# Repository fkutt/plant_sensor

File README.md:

# Czujnik wilgotności gleby (plant sensor)

Tania bateryjna sonda pojemnościowa do doniczek: ESP32-C3 SuperMini na podstawkach, ogniwo
LiFePO4 14500, elektrody wytrawione w PCB. Pomiar co godzinę, historia w sondzie, telefon przez
Bluetooth, opcjonalnie baza (drugi ESP32-C3 na USB) i Home Assistant przez MQTT.

**Aplikacja na telefon:** strona z folderu `docs/`, publikowana przez GitHub Pages
(adres w opisie repozytorium → *About*). Chrome na Androidzie / PC, na iPhonie przeglądarka Bluefy.

## Zawartość

| Folder | Co jest w środku |
| --- | --- |
| [`docs/`](docs) | Aplikacja na telefon (PWA, działa offline): kafelki czujników, wykresy, ustawienia sond i bazy |
| [`firmware/`](firmware) | Firmware ESPHome: sonda (`plant_sensor_universal*.yaml`) i baza (`plant_hub.yaml`) – opis w [`firmware/README_PL.md`](firmware/README_PL.md) |
| [`hardware/pcb_v2/`](hardware/pcb_v2) | Projekt PCB v2 w KiCad, model 3D płytki, pliki produkcyjne JLCPCB w `production/` |
| [`hardware/enclosure/`](hardware/enclosure) | Obudowa: model STEP i części do druku (STL) |
| [`manual/`](manual) | [Instrukcja obsługi](manual/instrukcja.md) z rysunkami |

## Szybki start

1. **PCB:** zamów płytki z `hardware/pcb_v2/production/` (instrukcja w `ORDER_JLCPCB.md`).
2. **Obudowa:** wydrukuj `plant_sensor_enc_top.stl` i `plant_sensor_enc_bottom.stl`.
3. **Firmware:** skopiuj `firmware/secrets.example.yaml` jako `firmware/secrets.yaml`, wpisz hasła, potem
   `python -m esphome run plant_sensor_universal_pl.yaml` (sonda) albo `python -m esphome run plant_hub.yaml` (baza).
4. **Telefon:** otwórz stronę aplikacji, *Połącz z bazą* (albo *Ustawienia → Sonda bez bazy*), zainstaluj jako aplikację.

## Wersje

| Element | Wersja |
| --- | --- |
| Firmware sondy | 0.9.11 alpha |
| Firmware bazy | 0.1.1 alpha |
| PCB | v2 (SuperMini na podstawkach) |

Plik `firmware/secrets.yaml` z hasłami jest wykluczony z repozytorium (`.gitignore`) – nie wrzucaj go.

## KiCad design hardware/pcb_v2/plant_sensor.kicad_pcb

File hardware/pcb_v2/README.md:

# Plant sensor v2 (SuperMini) – KiCad project

LiFePO4 14500 soil-moisture sensor with a plug-in ESP32-C3 SuperMini, BQ25170 charger set to
3.50 V, capacitive probe etched into the PCB, and footprints for optional air sensors.

Open `plant_sensor.kicad_pro` in KiCad 7, 8 or 9 (files are KiCad 7 format; newer versions
upgrade them when you save).

**Status: built and working (v2).** Production files for JLCPCB are in `production/` (see `production/ORDER_JLCPCB.md`). The 3D model of the assembled board: `plant_sensor_v2_assembly.step`.

## What is in the project

| File | Contents |
| --- | --- |
| `plant_sensor.kicad_sch` | Full schematic, one A3 sheet. Nets are joined by labels. Optional sensors are marked DNP. |
| `plant_sensor.kicad_pcb` | 2-layer board, 25 mm head / 20 mm stake, 181 mm long, routed, GND pours filled, DRC clean. |
| `plant_sensor.kicad_sym` | Project symbols: ESP32-C3 SuperMini, BQ25170DSG, probe electrodes. |
| `plant_sensor.pretty/` | Project footprints: SuperMini on sockets, 3.5 mm hole, probe electrodes. |
| `plant_sensor_BOM.csv` | Full parts list with what JLCPCB places and what you fit by hand. |

## Board

- **Back:** the Keystone 2460 holder for the 14500 cell, pushed against the left edge, and the
  ESP32-C3 SuperMini lying sideways above it on two 1x8 2.54 mm female sockets (detachable).
  USB-C sticks out ~1 mm at the left edge, the antenna end is at the right over a copper-free area
  (no pours or vias, both layers). Right of the holder: the optional JST-PH 4-pin side-entry
  connector J2 for an external I2C sensor; its mating face sticks out 2.0 mm past the right edge
  (flush with a 2 mm enclosure wall).
- **Front:** charger, battery divider and probe detector (placed by JLCPCB), plus the sensor area:
  SHT40 and LTR-303 at the top, SCD41 below them. The sensors themselves are hand-soldered only on the probes that need them;
  their power switch, pull-ups and capacitors are placed on every board.
- Head 25 mm wide with 1 mm top corners, all the way down to the soil line, where a 45° step goes to
  the 20 mm stake. Soil line at 83 mm, probe 98 mm, 2 mm fillets into the 45° bullet tip.
- One 3.5 mm enclosure hole right of the battery + pin (x = +8.25 mm); its edge is 5.0 mm above the
  soil line, leaving a band for the enclosure seal.
- Probe: 8 mm signal electrode in the middle, 3 mm ground horseshoe around it, both layers,
  under solder mask. Detector R13/D1/C11/R14 just above the 4 mm seal band.
- **Seal band:** 4 mm above the soil line (y 79–83 mm) is free of components on both sides (a DRC
  rule area enforces it); only tracks and ground copper cross it, under solder mask.

## SuperMini pinout used (check against your board!)

Seen from the SuperMini's component side, USB-C up:

| Right column (top→bottom) | Use | Left column (top→bottom) | Use |
| --- | --- | --- | --- |
| 5V | → charger input (VBUS) | GPIO5 | divider enable |
| GND | GND | GPIO6 | – |
| 3V3 | ← battery (VBAT) | GPIO7 | SDA |
| GPIO4 | probe drive (PWM) | GPIO8 | blue LED = status |
| GPIO3 | sensor power (low = on) | GPIO9 | BOOT button |
| GPIO2 | – | GPIO10 | SCL |
| GPIO1 | battery / 2 (ADC) | GPIO20 | – |
| GPIO0 | moisture (ADC) | GPIO21 | – |

Rows 15.24 mm apart, pins 2.54 mm. **Measure your SuperMini before ordering**: row-to-row distance
and that the pins sit centred along the 22.5 mm length.

## Preparing each SuperMini (hot air, 1 minute)

1. Remove the **red power LED** (always on, a few mA).
2. Remove the **3.3 V regulator** (5-pin chip next to USB-C). Reasons: it would push 3.3 V straight
   into the battery when USB is plugged in (uncontrolled charging, regulator gets hot), it leaks
   battery current backwards when unplugged, and it costs ~40 µA in sleep.
   Afterwards the battery powers the ESP32 and USB-C only charges and flashes, so **flash with the
   battery inserted**.

## Controls

- **RST** on the SuperMini = WAKE: measure now, blink the moisture code on the blue LED, send, sleep.
  Slow blinking = dry, fast = wet; a long 1.5 s glow first = battery low.
- **BOOT** on the SuperMini: hold it, press RST, release → download mode for USB flashing.
- Red **CHG** LED (front) lights while charging.

## Key values

| Ref | Value | Why |
| --- | --- | --- |
| R4 | 100 kΩ | BQ25170 VSET → LiFePO4 3.50 V |
| R3 | 1 kΩ | BQ25170 ISET → about 300 mA |
| R5 | 10 kΩ | BQ25170 TS without thermistor |
| R13 | 10 kΩ | Probe drive resistor; tune 4.7–47 kΩ for best dry/wet span |
| C11 / R14 | 100 nF / 1 MΩ | Peak detector hold and discharge |
| R16 / R17 | 100 kΩ / 100 kΩ | Battery divider; bottom goes to GPIO5, so no current while asleep |
| Q1 / R21 | AO3401A / 100 kΩ | Sensor supply switch; off in sleep |
| R19 / R20 | 4.7 kΩ | I2C pull-ups (on the switched supply) |

## Optional sensors (hand-soldered)

| Ref | Part | Measures | ESPHome |
| --- | --- | --- | --- |
| U3 | SHT40-AD1B | air temperature, humidity | `sht4x` |
| U4 | LTR-303ALS-01 | light, lux (0.01–64k) | `ltr_als_ps` |
| U5 | SCD41 | CO2 (single-shot, 5 s) | `scd4x` |
| U6 | RV-8523-C3 | real-time clock (crystal built in, ~150 nA, ±20 ppm), always on the battery | custom firmware (PCF8523-compatible) |
| J2 | JST S4B-PH-K-S (2.0 mm, side entry) | external I2C sensor; pins 1-4 = SCL SDA 3V3 GND (Grove order) | – |

Never fit a Li-ion 14500 (4.2 V): the cell connects straight to the ESP32-C3.

The current firmware is in [`../../firmware`](../../firmware) (pick `board: !include board_v2.yaml`).

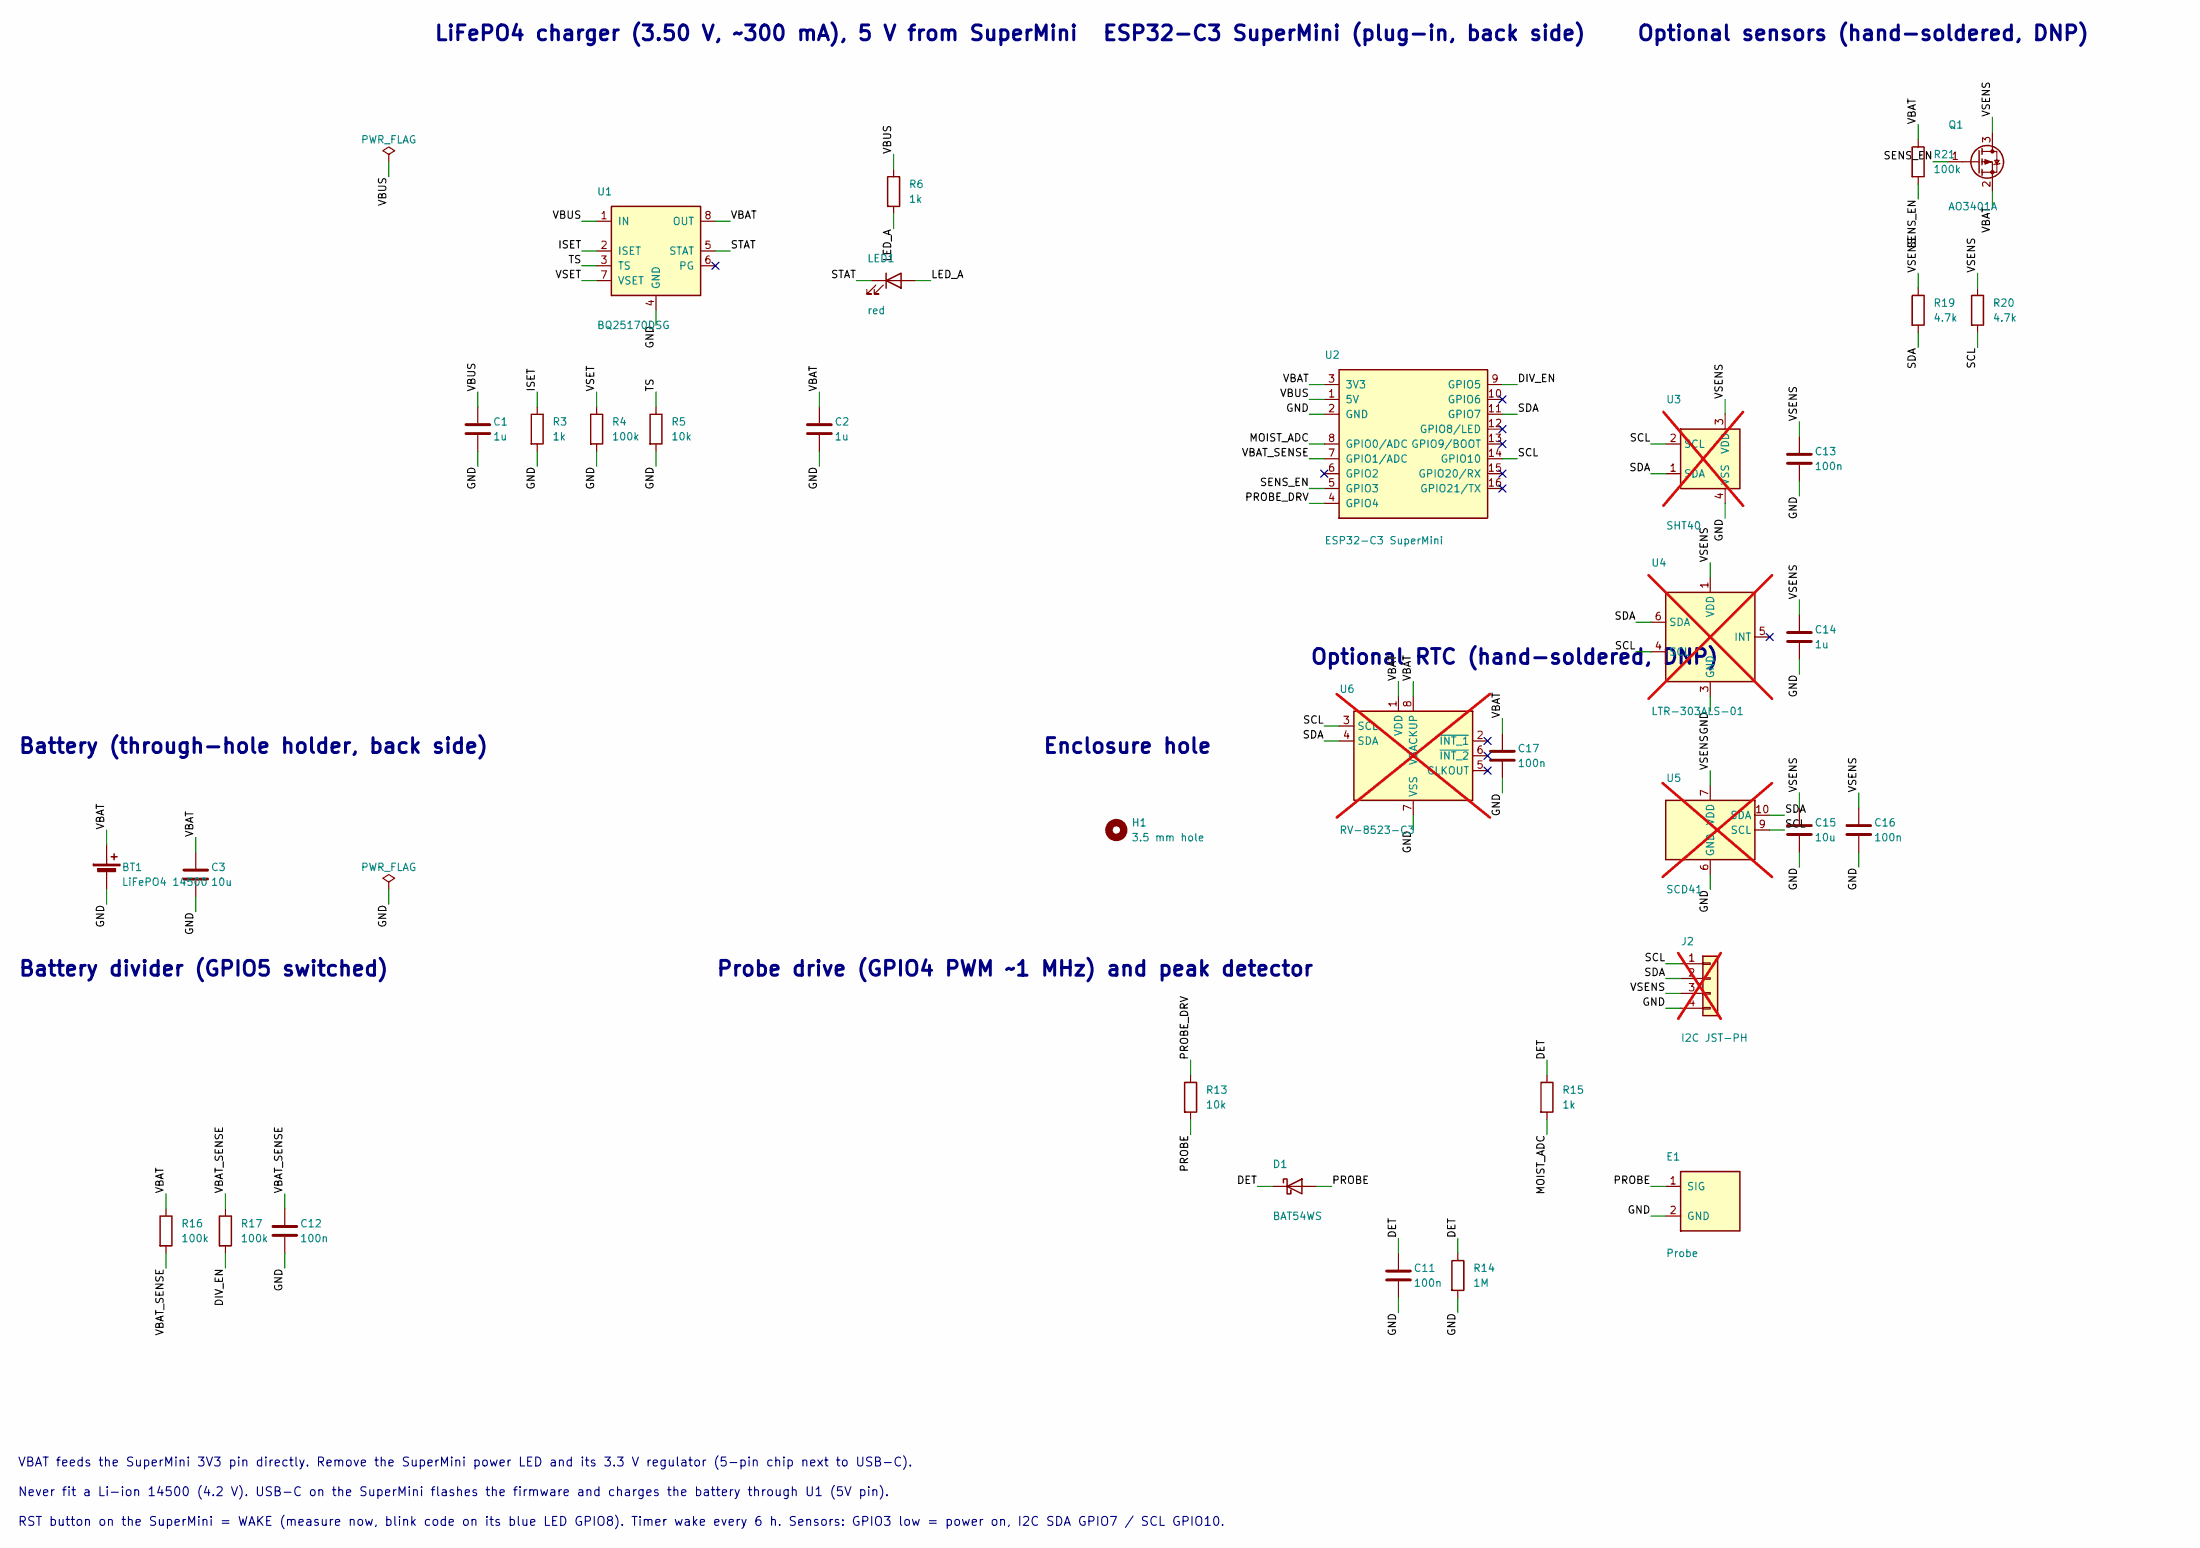
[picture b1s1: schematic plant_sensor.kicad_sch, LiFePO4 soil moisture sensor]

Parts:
BT1: LiFePO4 14500; BatteryHolder_Keystone_2460_1xAA; MPN Keystone 2460
C1, C2, C14: 1u; C_0603_1608Metric
C3, C15: 10u; C_0805_2012Metric
C11, C12, C13, C16, C17: 100n; C_0603_1608Metric
D1: BAT54WS; D_SOD-323; MPN BAT54WS
E1: Probe; Probe_Electrodes
H1: 3.5 mm hole; MountingHole_3.5mm
J2: I2C JST-PH; JST_PH_S4B-PH-K_1x04_P2.00mm_Horizontal; MPN JST S4B-PH-K-S; not fitted
LED1: red; LED_0603_1608Metric
Q1: AO3401A; SOT-23; MPN AO3401A
R3, R6, R15: 1k; R_0603_1608Metric
R4, R16, R17, R21: 100k; R_0603_1608Metric
R5, R13: 10k; R_0603_1608Metric
R14: 1M; R_0603_1608Metric
R19, R20: 4.7k; R_0603_1608Metric
U1: BQ25170DSG; WSON-8-1EP_2x2mm_P0.5mm_EP0.9x1.6mm; MPN BQ25170DSGR
U2: ESP32-C3 SuperMini; ESP32-C3_SuperMini_Socket; MPN ESP32-C3 SuperMini
U3: SHT40; Sensirion_DFN-4_1.5x1.5mm_P0.8mm_SHT4x_NoCentralPad; MPN SHT40-AD1B; not fitted
U4: LTR-303ALS-01; Lite-On_LTR-303ALS-01; MPN LTR-303ALS-01; not fitted
U5: SCD41; Sensirion_SCD4x-1EP_10.1x10.1mm_P1.25mm_EP4.8x4.8mm; MPN SCD41-D-R2; not fitted
U6: RV-8523-C3; RTC_SMD_MicroCrystal_C3_2.5x3.7mm; MPN RV-8523-C3; not fitted

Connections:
DET: C11.1, D1.1 (K), R14.1, R15.1
DIV_EN: R17.2, U2.9 (GPIO5)
GND: BT1.2 (-), C1.2, C2.2, C3.2, C11.2, C12.2, C13.2, C14.2, C15.2, C16.2, C17.2, E1.2 (GND), J2.4, R3.2, R4.2, R5.2, R14.2, U1.4 (GND), U1.9 (EP), U2.2 (GND), U3.4 (VSS), U4.3 (GND), U5.6 (GND), U5.20 (GND), U5.21 (GND), U6.7 (VSS)
ISET: R3.1, U1.2 (ISET)
LED_A: LED1.2 (A), R6.2
MOIST_ADC: R15.2, U2.8 (GPIO0/ADC)
PROBE: D1.2 (A), E1.1 (SIG), R13.2
PROBE_DRV: R13.1, U2.4 (GPIO4)
SCL: J2.1, R20.2, U2.14 (GPIO10), U3.2 (SCL), U4.4 (SCL), U5.9 (SCL), U6.3 (SCL)
SDA: J2.2, R19.2, U2.11 (GPIO7), U3.1 (SDA), U4.6 (SDA), U5.10 (SDA), U6.4 (SDA)
SENS_EN: Q1.1 (G), R21.2, U2.5 (GPIO3)
STAT: LED1.1 (K), U1.5 (STAT)
TS: R5.1, U1.3 (TS)
VBAT: BT1.1 (+), C2.1, C3.1, C17.1, Q1.2 (S), R16.1, R21.1, U1.8 (OUT), U2.3 (3V3), U6.1 (VDD), U6.8 (VBACKUP)
VBAT_SENSE: C12.1, R16.2, R17.1, U2.7 (GPIO1/ADC)
VBUS: C1.1, R6.1, U1.1 (IN), U2.1 (5V)
VSENS: C13.1, C14.1, C15.1, C16.1, J2.3, Q1.3 (D), R19.1, R20.1, U3.3 (VDD), U4.1 (VDD), U5.7 (VDD), U5.19 (VDD)
VSET: R4.1, U1.7 (VSET)

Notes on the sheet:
LiFePO4 charger (3.50 V, ~300 mA), 5 V from SuperMini
Battery (through-hole holder, back side)
ESP32-C3 SuperMini (plug-in, back side)
Optional sensors (hand-soldered, DNP)
Optional RTC (hand-soldered, DNP)
Enclosure hole
Battery divider (GPIO5 switched)
Probe drive (GPIO4 PWM ~1 MHz) and peak detector
VBAT feeds the SuperMini 3V3 pin directly. Remove the SuperMini power LED and its 3.3 V regulator (5-pin chip next to USB-C).
Never fit a Li-ion 14500 (4.2 V). USB-C on the SuperMini flashes the firmware and charges the battery through U1 (5V pin).
RST button on the SuperMini = WAKE (measure now, blink code on its blue LED GPIO8). Timer wake every 6 h. Sensors: GPIO3 low = power on, I2C SDA GPIO7 / SCL GPIO10.

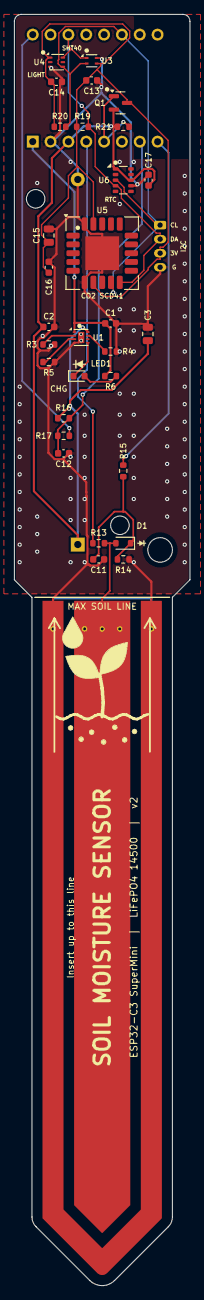
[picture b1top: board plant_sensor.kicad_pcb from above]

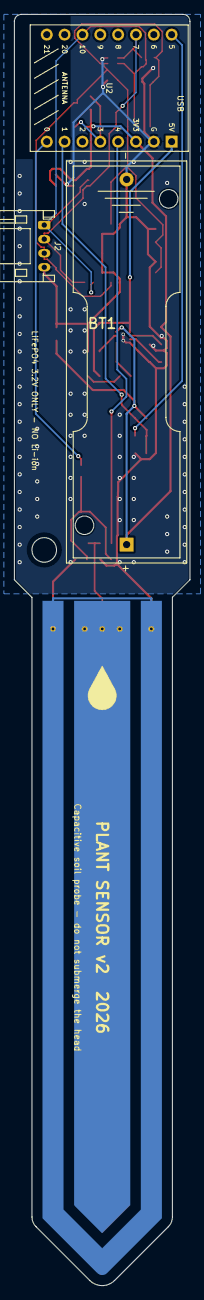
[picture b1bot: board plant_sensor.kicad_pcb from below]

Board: 2 copper layers, 25.0 x 181.0 mm, 35 parts (3 on the bottom side), 18 nets.

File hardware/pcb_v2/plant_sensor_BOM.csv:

Item,Designator,Qty,Value,Package,Manufacturer,Manufacturer Part Number,Description,Type,Place,Link
1,"C1, C2, C14",3,1u,C_0603_1608Metric,Any,,Ceramic capacitor 1u 16V+ X5R/X7R 0603,SMD,Yes,
2,"C3, C15",2,10u,C_0805_2012Metric,Any,,Ceramic capacitor 10u 10V X5R/X7R 0805,SMD,Yes,
3,"C11, C12, C13, C16, C17",5,100n,C_0603_1608Metric,Any,,Ceramic capacitor 100n 16V+ X5R/X7R 0603,SMD,Yes,
4,D1,1,BAT54WS-TP,D_SOD-323,MCC,BAT54WS-TP,Schottky diode 30V SOD-323,SMD,Yes,https://www.lcsc.com/product-detail/schottky-diodes_mcc-micr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
5,LED1,1,red,LED_0603_1608Metric,Any,,LED red 0603,SMD,Yes,
6,Q1,1,AO3401A,SOT-23,Alpha & Omega,AO3401A,"Sensor power switch, P-MOSFET SOT-23 (off unless GPIO3 low)",SMD,Yes,https://www.lcsc.com/product-detail/C15127.html
7,"R3, R6, R15",3,1k,R_0603_1608Metric,Any,,Resistor 1k 1% 0603,SMD,Yes,
8,"R4, R16, R17, R21",4,100k,R_0603_1608Metric,Any,,Resistor 100k 1% 0603,SMD,Yes,
9,"R5, R13",2,10k,R_0603_1608Metric,Any,,Resistor 10k 1% 0603,SMD,Yes,
10,R14,1,1M,R_0603_1608Metric,Any,,Resistor 1M 1% 0603,SMD,Yes,
11,"R19, R20",2,4.7k,R_0603_1608Metric,Any,,Resistor 4.7k 1% 0603,SMD,Yes,
12,U1,1,BQ25170DSGR,WSON-8-1EP_2x2mm_P0.5mm_EP0.9x1.6mm,Texas Instruments,BQ25170DSGR,"LiFePO4 linear charger 800mA, WSON-8 2x2",SMD,Yes,https://www.lcsc.com/product-detail/battery-management_texas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
13,BT1,1,LiFePO4 14500,BatteryHolder_Keystone_2460_1xAA,Keystone,2460,"1xAA/14500 holder, PC pins (THT) - DO NOT PLACE (hand solder, back side)",THT,No (hand),https://www.digikey.com/en/products/detail/keystone-electron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
14,J2,1,I2C JST-PH,JST_PH_S4B-PH-K_1x04_P2.00mm_Horizontal,JST,S4B-PH-K-S,"OPTIONAL JST PH 2.0 mm 4-pin side entry S4B-PH-K-S, back side (hand solder)",THT,No (hand),https://www.lcsc.com/search?q=S4B-PH-K-S
15,U2,1,ESP32-C3 SuperMini,ESP32-C3_SuperMini_Socket,Nologo / generic,ESP32-C3 SuperMini,"ESP32-C3 board, USB-C, 22.5x18 mm - plug-in on 2x 1x8 sockets; remove power LED + 3.3V regulator",THT,No (hand),https://jlcpcb.com/partdetail/JLCPCBAssembly-ESP32C3SuperMin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
16,U3,1,SHT40-AD1B,Sensirion_DFN-4_1.5x1.5mm_P0.8mm_SHT4x_NoCentralPad,Sensirion,SHT40-AD1B,"OPTIONAL temperature + humidity, DFN-4 1.5x1.5 (hot air)",SMD,No (hand),https://www.lcsc.com/search?q=SHT40-AD1B
17,U4,1,LTR-303ALS-01,Lite-On_LTR-303ALS-01,Lite-On,LTR-303ALS-01,"OPTIONAL ambient light sensor, 2x2 ChipLED-6 (hot air)",SMD,No (hand),https://www.lcsc.com/search?q=LTR-303ALS-01
18,U5,1,SCD41-D-R2,Sensirion_SCD4x-1EP_10.1x10.1mm_P1.25mm_EP4.8x4.8mm,Sensirion,SCD41-D-R2,"OPTIONAL CO2 sensor, 10.1x10.1 LGA (hot air)",SMD,No (hand),https://www.lcsc.com/search?q=SCD41
19,U6,1,RV-8523-C3,RTC_SMD_MicroCrystal_C3_2.5x3.7mm,Micro Crystal,RV-8523-C3,"OPTIONAL real-time clock, crystal built in, C3 2.5x3.7 (hot air)",SMD,No (hand),https://www.lcsc.com/search?q=RV-8523-C3
20,(U2 socket),2,1x8 female,2.54 mm,Any,,Female pin socket 1x8 2.54 mm (or round-pin machined for a lower stack) - hand solder on the back,THT,No (hand),

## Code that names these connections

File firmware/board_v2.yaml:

# Pin map: v2 board (PCB "PLANT SENSOR v2") with an ESP32-C3 SuperMini.
# Choose the board in the top-level file (packages: board: !include ...).
substitutions:
  pin_moist: GPIO0
  pin_vbat: GPIO1
  pin_probe: GPIO4
  pin_div: GPIO5
  pin_led: GPIO8
  pin_sens: GPIO3
  pin_sda: GPIO7
  pin_scl: GPIO10
  board_name: "v2 SuperMini"
